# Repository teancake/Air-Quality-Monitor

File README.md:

# Air-Quality-Monitor
Schematic and PCB design of an air quality monitor.

### Description ###
This WiFi switch module utilises the [ESP-12E/F adaptor](https://github.com/teancake/ESP8266-ESP12-Adaptor "ESP-12E/F Adaptor").
### Programs ###
There are two ways of programming this piece of hardware:
1. Program both the AVR chip on the Arduino board and the ESP8266 chip on the ESP-12E/F board.
2. Program only the AVR chip on the Arduino board. 

The first approach is recommended, since it exhibits more flexibility and the program is more structured. For this approach, please refer to 
[Arduino program](https://github.com/teancake/Indoor-Air-Quality-Monitoring-and-Control-System/tree/master/software/sensor_unit_software/officenv_arduino_v2) and [ESP8266 program](https://github.com/teancake/Indoor-Air-Quality-Monitoring-and-Control-System/tree/master/software/sensor_unit_software/officenv_esp12ef_v1) in the [Indoor-Air-Quality-Monitoring-and-Control-System](https://github.com/teancake/Indoor-Air-Quality-Monitoring-and-Control-System) repository, respectively. 

If you insist to use the second approach, please leave the original firmware in the ESP8266 chip as it is and use [Arduino program](https://github.com/teancake/Indoor-Air-Quality-Monitoring-and-Control-System/tree/master/software/sensor_unit_software/officenv_arduino_v1) for the Arduino board. In this way, you may also need a TCP server to receive the data from the sensor, an example of the server program is [here, publish_office_air_quality.py](https://github.com/teancake/Indoor-Air-Quality-Monitoring-and-Control-System/tree/master/software/server_software) in the [Indoor-Air-Quality-Monitoring-and-Control-System](https://github.com/teancake/Indoor-Air-Quality-Monitoring-and-Control-System) repository.

For both approaches, make sure the baud rate of the Arduino and the ESP-12E/F boards are the same. If you use the second approach, the default baud rate of the ESP-12 board is 115200, which can be changed (say to 57600) using an AT command as `AT+CIOBAUD=57600` and checked by `AT+CIOBAUD?`. I was not successful at changing the baud rate of the ESP-12 board, but was successful on an ESP-03 board. Besides, the baud rate of 115200 was exceedingly unreliable between Arduino Pro Mini 3.3V version and ESP8266, and I have to reduce it to at most 57600 in order to make the communication work. I had no idea of why these mysteries happened, so if anybody finds the reason, please do let me know.
 
### The Finished Board ###

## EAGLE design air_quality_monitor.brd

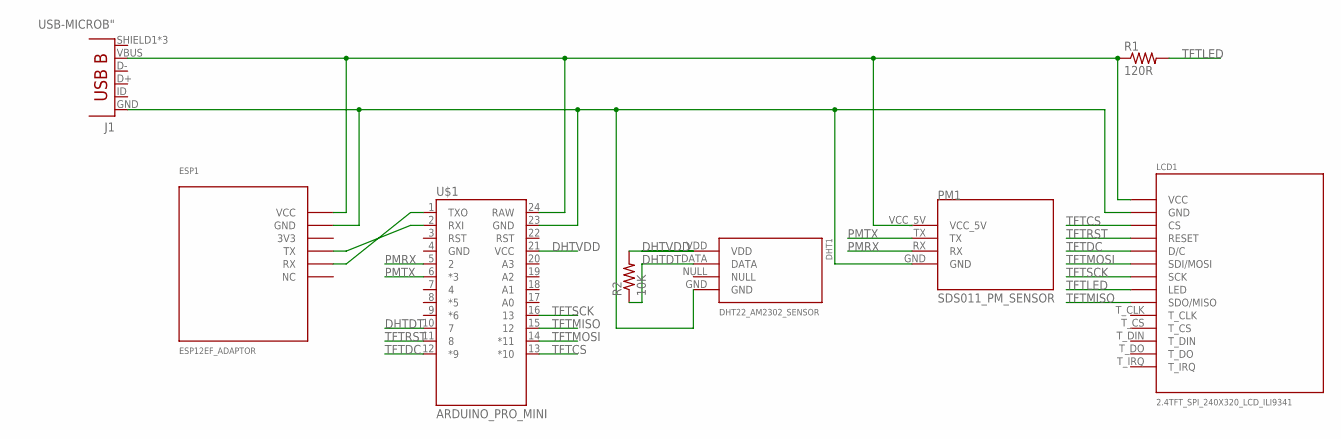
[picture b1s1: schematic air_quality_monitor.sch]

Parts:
DHT1: DHT22_AM2302_SENSOR
ESP1: ESP12EF_ADAPTOR
J1: USB-MICROB"; USB-B-MICRO-SMD_V03
LCD1: 2.4TFT_SPI_240X320_LCD_ILI9341
PM1: SDS011_PM_SENSOR
R1: 120R; 0603-RES
R2: 10K; 0603-RES
U$1: ARDUINO_PRO_MINI

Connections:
DHTDT: DHT1.DATA, R2.1, U$1.10 (7)
DHTVDD: DHT1.VDD, R2.2, U$1.21 (VCC)
unnamed: DHT1.GND, ESP1.GND, J1.GND, LCD1.GND, PM1.GND, U$1.23 (GND)
unnamed: ESP1.VCC, J1.VBUS, LCD1.VCC, PM1.VCC_5V, R1.1, U$1.24 (RAW)
unnamed: ESP1.TX, U$1.2 (RXI)
unnamed: ESP1.RX, U$1.1 (TXO)
PMRX: PM1.RX, U$1.5 (2)
PMTX: PM1.TX, U$1.6 (*3)
TFTCS: LCD1.CS, U$1.13 (*10)
TFTDC: LCD1.D/C, U$1.12 (*9)
TFTLED: LCD1.LED, R1.2
TFTMISO: LCD1.SDO/MISO, U$1.15 (12)
TFTMOSI: LCD1.SDI/MOSI, U$1.14 (*11)
TFTRST: LCD1.RESET, U$1.11 (8)
TFTSCK: LCD1.SCK, U$1.16 (13)

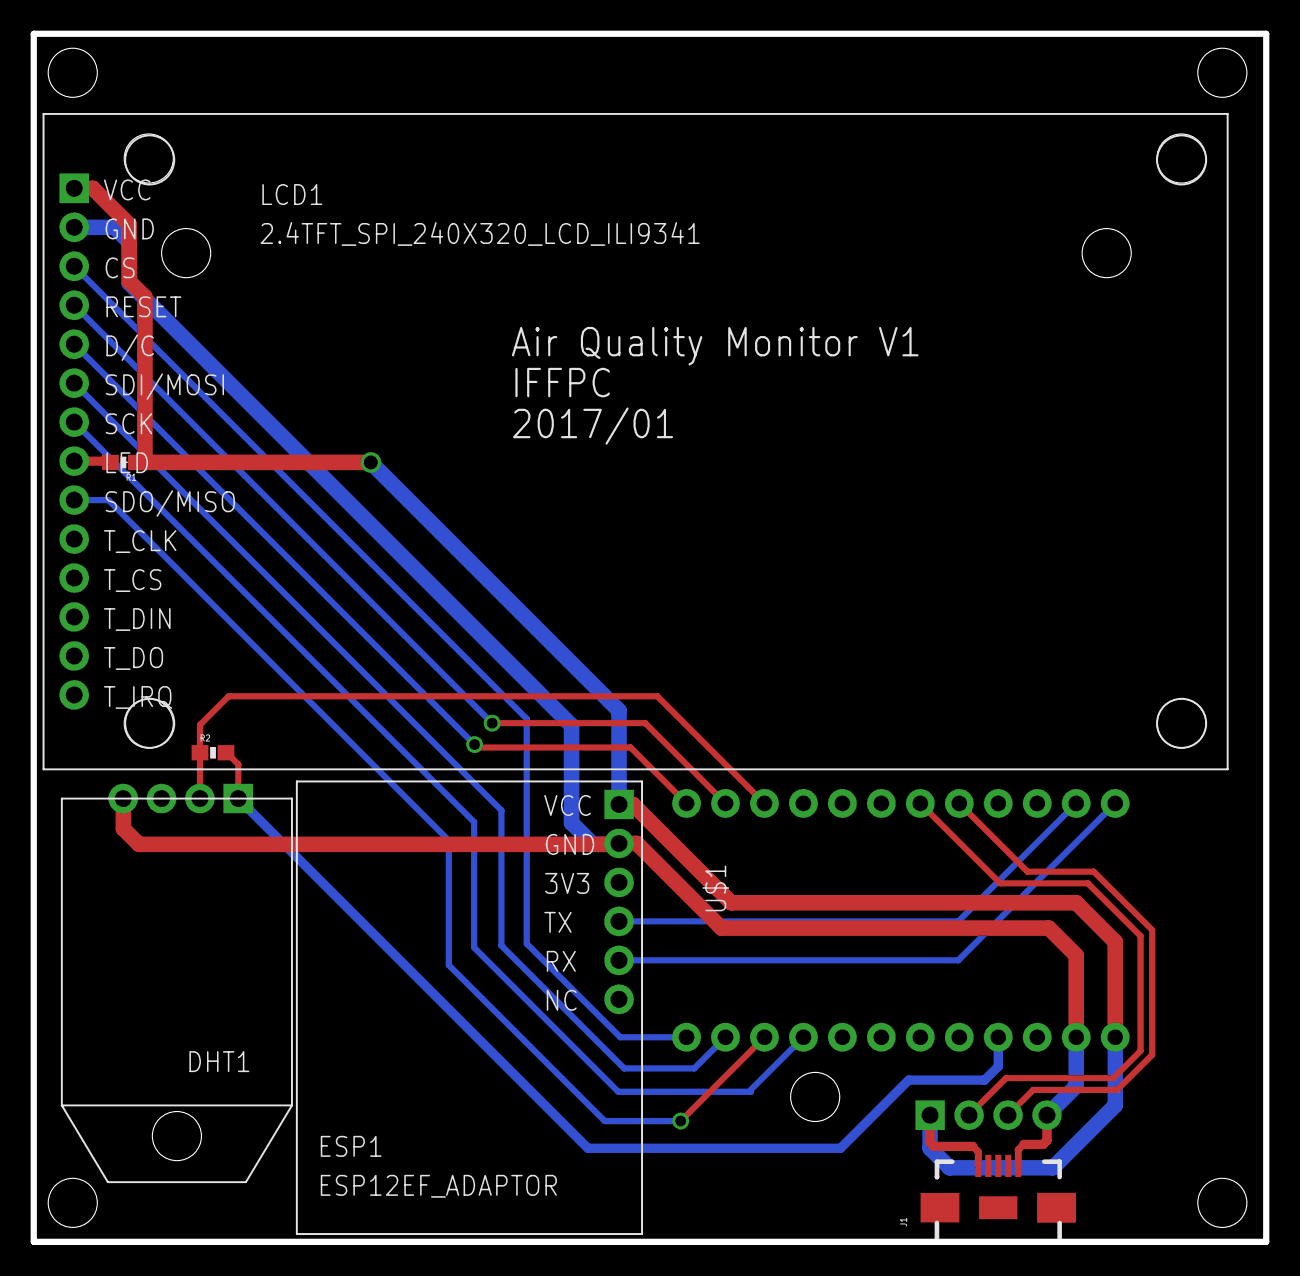
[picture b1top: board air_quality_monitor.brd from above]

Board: 2 copper layers, 80.3 x 78.7 mm, 8 parts (1 on the bottom side), 15 nets.

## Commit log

2017-02-17 initial release
2017-02-27 add finished board and modify readme accordingly
